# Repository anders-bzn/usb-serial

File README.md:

# USB to RS232 serial converter
This is a galvanically isolated USB to RS2332 serial adapter. The repository includes project files for both a PCB and an enclosure.

## Short data:
- One USB-C connector and one DB25 D-SUB male connector
- Full ±12V voltage swing on the RS232 side
- Rx/Tx and RTS and CTS signals are available
- Galvanic isolation provided by the MAX22246
- USB to serial conversion handled by the CP2102
- Supported data formats:
    - Data bits: 5, 6, 7, and 8
    - Stop bits: 1, 1.5, and 2
    - Parity: Odd, even, mark, space and none
    - Baud rates from 300 to 921600
- Supports serial break

## Tools used
This project was created using:
- [KiCad 9.0](https://www.kicad.org/) and [kicad-jlcpcb-tools](https://github.com/Bouni/kicad-jlcpcb-tools) plugin for generating PCB and fabrication files
- [FreeCAD 1.0.2](https://www.freecad.org/downloads.php?lang=en) for 3D modeling the enclosure

## Assembly Instructions
To ensure easy and successful assembly, follow these steps:

1. Mount all surface-mount components.
All necessary files are included for ordering fully assembled PCBs (apart from through hole components) from JLCPCB.
2.  Mount all through-hole components.
This includes the 3mm green LED and the DC/DC converter.
3. Mount the D-SUB connector:
    * Place the PCB into the enclosure so the USB connector and LED aligned correctly.
    * Position the D-SUB connector and screw it in place using the #4-40 standoffs and solder it in place.
    * Disassemble the PCB and solder the other side of the D-SUB connector.
4. Final assembly
    * Reassemble the PCB in the enclosure.
    * Slide on the lid.
    * Secure the lid using 2 × M2.5 × 14mm countersunk machine screws.

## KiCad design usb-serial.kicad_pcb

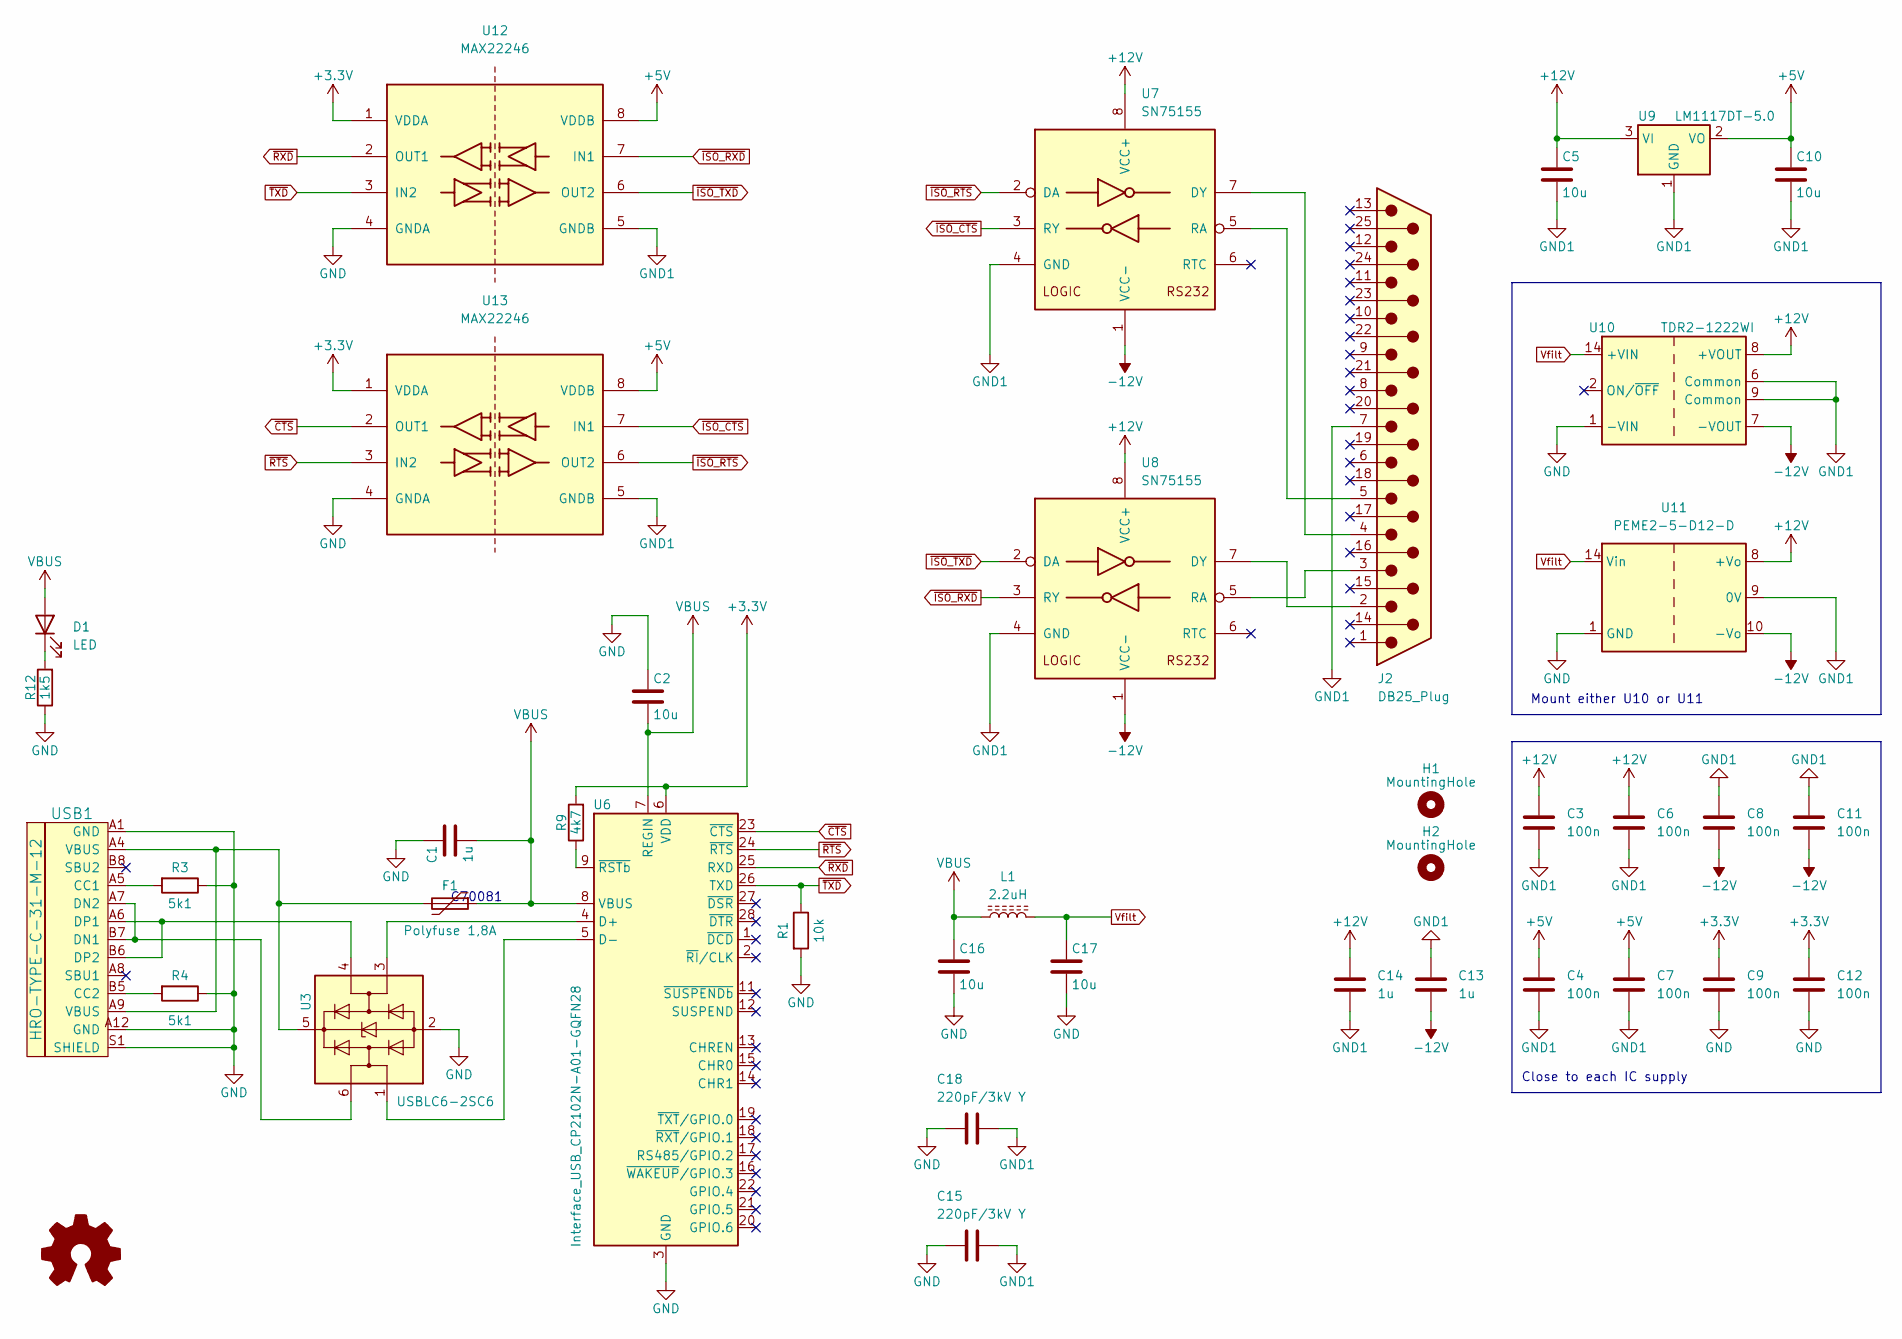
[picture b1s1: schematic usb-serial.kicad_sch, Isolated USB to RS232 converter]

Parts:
C1, C13, C14: 1u; C_0805_2012Metric
C2, C5, C10, C16, C17: 10u; C_0805_2012Metric
C3, C4, C6, C7, C8, C9, C11, C12: 100n; C_0402_1005Metric
C15, C18: 220pF/3kV Y; C_1812_4532Metric
D1: LED; LED_D3.0mm_Horizontal_O3.81mm_Z10.0mm
F1: Polyfuse 1,8A; Fuse_1206_3216Metric
H1, H2: MountingHole; MountingHole_3.2mm_M3
J2: DB25_Plug; DSUB-25_Male_EdgeMount_P2.77mm
L1: 2.2uH; L_6.3x6.3_H3
R1: 10k; R_0402_1005Metric
R3, R4: 5k1; R_0402_1005Metric
R9: 4k7; R_0402_1005Metric
R12: 1k5; R_0402_1005Metric
U3: USBLC6-2SC6; SOT-23-6
U6: Interface_USB_CP2102N-A01-GQFN28; QFN-28-1EP_5x5mm_P0.5mm_EP3.35x3.35mm
U7, U8: SN75155; SO-8_3.9x4.9mm_P1.27mm
U9: LM1117DT-5.0; SOT-223-3_TabPin2
U10: TDR2-1222WI; Converter_DCDC_TRACO_TDR2-xxxxWI
U11: PEME2-5-D12-D; Converter_DCDC_CUI_INC_PEME2-xx-Dxx-D
U12, U13: MAX22246
USB1: HRO-TYPE-C-31-M-12; USB_C_Receptacle_HRO_TYPE-C-31-M-12

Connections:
+3.3V: C9.1, C12.1, R9.2, U6.6 (VDD), U12.1 (VDDA), U13.1 (VDDA)
+5V: C4.1, C7.1, C10.1, U9.2 (VO), U12.8 (VDDB), U13.8 (VDDB)
+12V: C3.1, C5.1, C6.1, C14.2, U7.8 (VCC+), U8.8 (VCC+), U9.3 (VI), U10.8 (+VOUT), U11.8 (+Vo)
-12V: C8.2, C11.2, C13.1, U7.1 (VCC-), U8.1 (VCC-), U10.7 (-VOUT), U11.10 (-Vo)
GND: C1.1, C2.1, C9.2, C12.2, C15.2, C16.2, C17.2, C18.2, R1.2, R3.1, R4.1, R12.1, U3.2 (GND), U6.3 (GND), U6.29 (GND), U10.1 (-VIN), U11.1 (GND), U12.4 (GNDA), U13.4 (GNDA), USB1.A1 (GND), USB1.A12 (GND), USB1.S1 (SHIELD)
GND1: C3.2, C4.2, C5.2, C6.2, C7.2, C8.1, C10.2, C11.1, C13.2, C14.1, C15.1, C18.1, J2.7, U7.4 (GND), U8.4 (GND), U9.1 (GND), U10.6 (Common), U10.9 (Common), U11.9 (0V), U12.5 (GNDB), U13.5 (GNDB)
unnamed: D1.1 (K), R12.2
unnamed: F1.2, U3.5 (VBUS), USB1.A4 (VBUS), USB1.A9 (VBUS)
unnamed: U3.3 (I/O2), U6.4 (D+)
unnamed: U3.1 (I/O1), U6.5 (D-)
unnamed: R9.1, U6.9 (~RSTb)
unnamed: J2.4, U7.7 (DY)
unnamed: J2.5, U7.5 (RA)
unnamed: J2.2, U8.7 (DY)
unnamed: J2.3, U8.5 (RA)
unnamed: R3.2, USB1.A5 (CC1)
unnamed: R4.2, USB1.B5 (CC2)
unnamed: U3.6 (I/O1), USB1.A7 (DN2), USB1.B7 (DN1)
unnamed: U3.4 (I/O2), USB1.A6 (DP1), USB1.B6 (DP2)
VBUS: C1.2, C2.2, C16.1, D1.2 (A), F1.1, L1.1, U6.7 (REGIN), U6.8 (VBUS)
Vfilt: C17.1, L1.2, U10.14 (+VIN), U11.14 (Vin)
~CTS: U6.23 (~CTS), U13.2 (OUT1)
~ISO_CTS: U7.3 (RY), U13.7 (IN1)
~ISO_RTS: U7.2 (DA), U13.6 (OUT2)
~ISO_RXD: U8.3 (RY), U12.7 (IN1)
~ISO_TXD: U8.2 (DA), U12.6 (OUT2)
~RTS: U6.24 (~RTS), U13.3 (IN2)
~RXD: U6.25 (RXD), U12.2 (OUT1)
~TXD: R1.1, U6.26 (TXD), U12.3 (IN2)

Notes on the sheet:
Close to each IC supply
C70081
Mount either U10 or U11

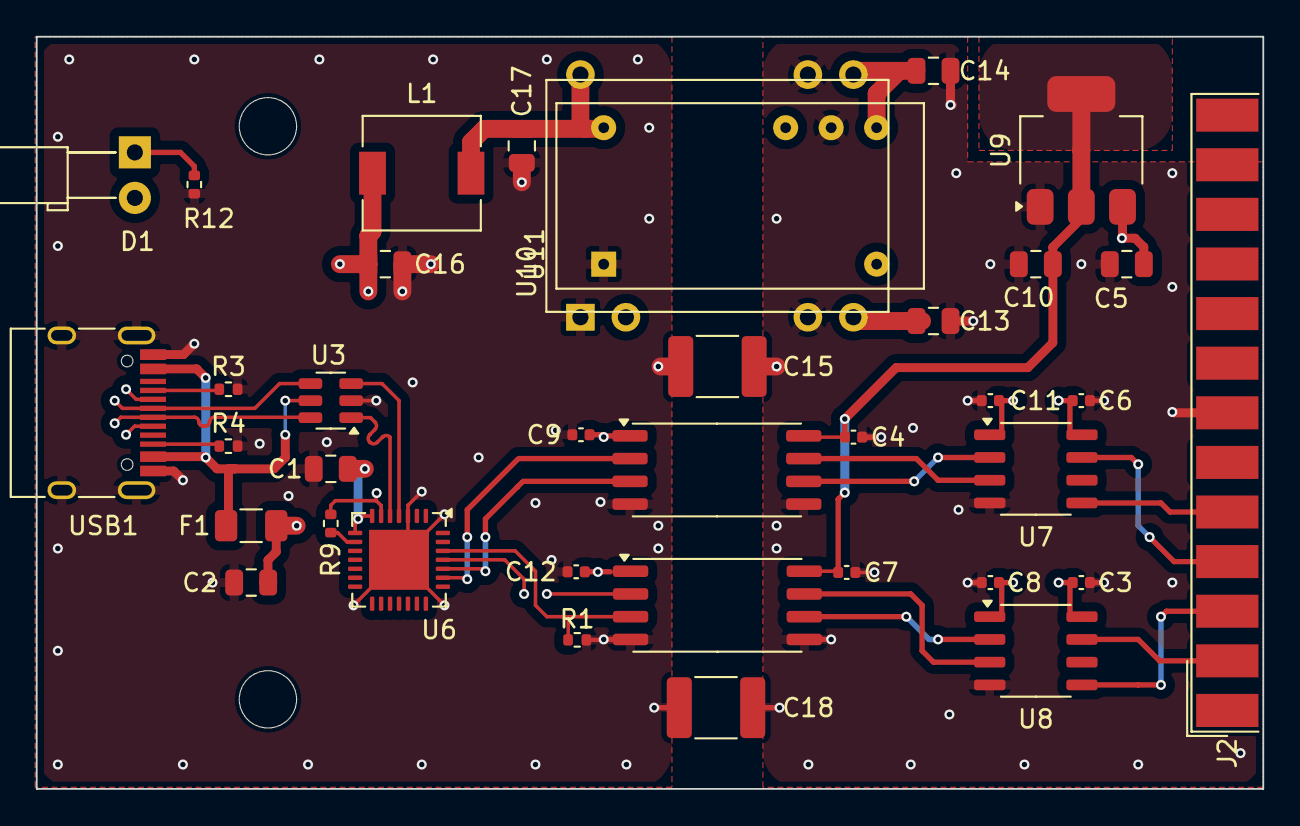
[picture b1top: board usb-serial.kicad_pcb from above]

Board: 4 copper layers, 68.5 x 42.0 mm, 39 parts (0 on the bottom side), 29 nets.

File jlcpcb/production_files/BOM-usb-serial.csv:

Comment,Designator,Footprint,LCSC,Quantity
100n,"C11,C12,C3,C4,C6,C7,C8,C9",C_0402_1005Metric,C307331,8
10k,R1,R_0402_1005Metric,C60490,1
10u,"C10,C16,C17,C2,C5",C_0805_2012Metric,C15850,5
1k5,R12,R_0402_1005Metric,C114759,1
1u,"C1,C13,C14",C_0805_2012Metric,C28323,3
2.2uH,L1,L_6.3x6.3_H3,C2849520,1
220pF/3kV Y,"C15,C18",C_1812_4532Metric,C2940747,2
4k7,R9,R_0402_1005Metric,C105870,1
5k1,"R3,R4",R_0402_1005Metric,C105872,2
HRO-TYPE-C-31-M-12,USB1,USB_C_Receptacle_HRO_TYPE-C-31-M-12,C165948,1
Interface_USB_CP2102N-A01-GQFN28,U6,QFN-28-1EP_5x5mm_P0.5mm_EP3.35x3.35mm,C964632,1
LM1117DT-5.0,U9,SOT-223-3_TabPin2,C41202,1
MAX22246,"U12,U13",MAX22246,C7457939,2
"Polyfuse 1,8A",F1,Fuse_1206_3216Metric,C70081,1
SN75155,"U7,U8",SO-8_3.9x4.9mm_P1.27mm,C139383,2
USBLC6-2SC6,U3,SOT-23-6,C7519,1
PEME2-5-D12-D,U11,Converter_DCDC_CUI_INC_PEME2-xx-Dxx-D,,1
LED,D1,LED_D3.0mm_Horizontal_O3.81mm_Z10.0mm,,1
MountingHole,H2,MountingHole_3.2mm_M3,,1
DB25_Plug,J2,DSUB-25_Male_EdgeMount_P2.77mm,,1
TDR2-1222WI,U10,Converter_DCDC_TRACO_TDR2-xxxxWI,,1
MountingHole,H1,MountingHole_3.2mm_M3,,1

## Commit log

2024-03-07 Add files
2024-03-07 Add fabrication fies
2024-03-07 Update project file
2024-03-07 Add pdf drawing
2024-04-03 EMC filter according to DC/DC datasheet
2024-04-03 Print drawing sheet on pdf
2025-10-07 mechanics: Add 3D model
2025-10-07 usb-serial: Change opto to MAX 22246 isolator.
2025-10-07 Added more files to ignore
2025-10-07 jlcpcb: Updated production files
    Updated production files to reflect the updated schematics and PCB.
2025-10-08 Updated 3D image of PCB
2025-10-08 REAdME.md: Update
    - Added short data on the converter
    - Added assembly instructions
    - Added used tools
2025-10-16 usb-serial: Fix swapped RXD and TXD
2025-10-16 mechanics: Adjusted countersink size
2025-10-30 mechanics: Add threads to model
    Model threads.
    - #4-40 to the DSUB stand offs
    - M2.5 to the screws that holds the lid
2025-11-03 Re-generate production files
2026-01-19 Add resistor to fix serial break support
    There must be pulldown resistor of 10k from TxD to GND on the CP2102 to
    make serial break to work.
    Also, updated to use KiCad 9.0 as PCB design tool.
